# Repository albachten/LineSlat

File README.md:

# LineSlat - Daisy-chained fireworks controllers for line effects

This is an ARM Cortex M0 board with:
* SAMD21 cpu
* USB for programming & serial debug
* Cortex Debug connector for bootloader install & hw debug
* 8 Pairs of PyroClips (8 cues per station)
* 2 RJ45 connectors for daisy-chaining (power & serial comm)
* 915MHz Hope RFM95 Lora module (only populated in the master station)
* Powered by 18V external LiPo battery pack (master station only, slave stations are powered by the master station)
* OLED display

Note: this board can also be used as an 8 cue standalone fireworks controller.

[Schematic pdf](v2.0/LineSlat.pdf)

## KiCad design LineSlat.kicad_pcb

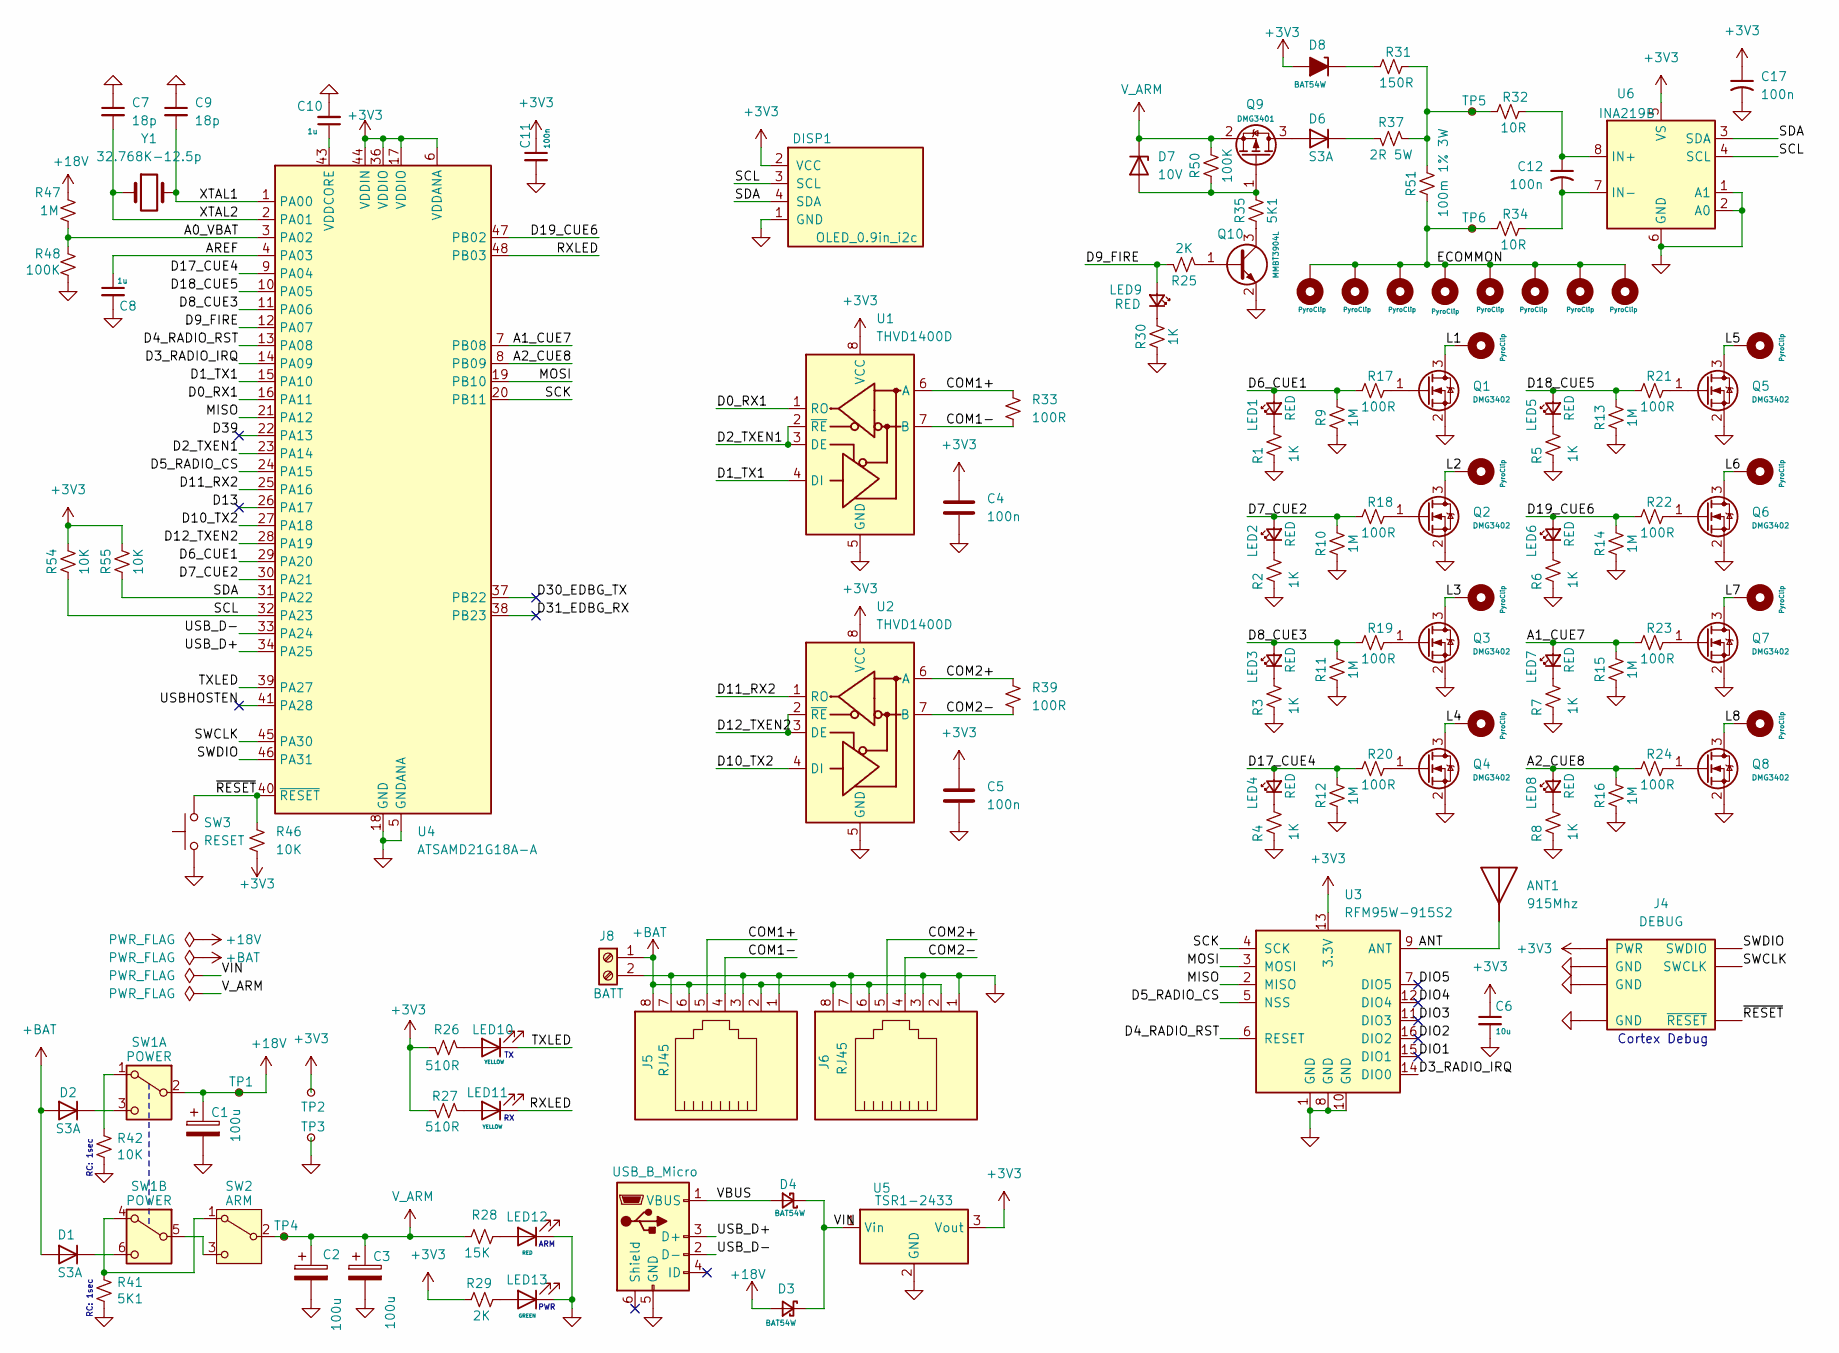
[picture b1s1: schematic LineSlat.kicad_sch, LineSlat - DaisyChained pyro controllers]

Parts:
ANT1: 915Mhz; Antenna915MHzSimpleCoil; Manufacturer_Part_Number 4269; Mouser Part Number 485-4269
C1, C2, C3: 100u; CP_Radial_D6.3mm_P2.50mm; Mouser_Part_Number 710-860010573007
C4, C5, C11, C12, C17: 100n; C_0603_1608Metric
C6: 10u; C_0603_1608Metric
C7, C9: 18p; C_0603_1608Metric
C8, C10: 1u; C_0603_1608Metric
CLIP1, CLIP2, CLIP3, CLIP4, CLIP5, CLIP6, CLIP7, CLIP8: PyroClip; PyroClipBlack; Mouser_Part_Number N/A
CLIP9, CLIP10, CLIP11, CLIP12, CLIP13, CLIP14, CLIP15, CLIP16: PyroClip; PyroClipRed; Mouser_Part_Number N/A
D1, D2, D6: S3A; D_SMC; Mouser_Part_Number 512-S3A
D3, D4, D8: BAT54W; D_SOD-123; Mouser_Part_Number 78-BAT54W-HG3-18
D7: 10V; SOT-23; Mouser_Part_Number 863-BZX84C10LT1G
DISP1: OLED_0.9in_i2c; OLED_0.9in_i2c_weewooday; Mouser_Part_Number N/A
J4: DEBUG; CortexDebugSMD; Mouser_Part_Number 640-BD12510A305580LB
J5, J6: RJ45; RJ45_SS-700810-NF; Mouser_Part_Number 530-SS-700810-NF
J7: USB_B_Micro; USB_Micro-B_Amphenol_10118194_Horizontal; Mouser_Part_Number 649-10118194-0011LF
J8: BATT; TerminalBlock_1x02_P5.08mm; Mouser_Part_Number 649-VI02215200J0G
LED1, LED2, LED3, LED4, LED5, LED6, LED7, LED8, LED9, LED12: RED; LED_0805_2012Metric; Mouser_Part_Number 710-150080RS75000
LED10, LED11: YELLOW; LED_0805_2012Metric; Mouser_Part_Number 710-150080YS75000
LED13: GREEN; LED_0805_2012Metric; Mouser_Part_Number 710-150080RS75000
Q1, Q2, Q3, Q4, Q5, Q6, Q7, Q8: DMG3402; SOT-23; Mouser_Part_Number 621-DMG3402L-7
Q9: DMG3401; SC-59; Mouser_Part_Number 621-DMP3099L-13
Q10: MMBT3904L; SOT-23; Mouser_Part_Number 771-MMBT3904VL
R1, R2, R3, R4, R5, R6, R7, R8, R30: 1K; R_0603_1608Metric
R9, R10, R11, R12, R13, R14, R15, R16, R47: 1M; R_0603_1608Metric
R17, R18, R19, R20, R21, R22, R23, R24, R33, R39: 100R; R_0603_1608Metric
R25, R29: 2K; R_0603_1608Metric
R26, R27: 510R; R_0603_1608Metric
R28: 15K; R_0603_1608Metric
R31: 150R; R_0603_1608Metric
R32, R34: 10R; R_0603_1608Metric
R35, R41: 5K1; R_0603_1608Metric
R37: 2R 5W; R_Axial_Power_L25.0mm_W6.4mm_P27.94mm; Mouser_Part_Number 588-TUW5J2R0E
R42, R46, R54, R55: 10K; R_0603_1608Metric
R48, R50: 100K; R_0603_1608Metric
R51: 100m 1% 3W; R_2512_6332Metric
SW1: POWER; DPDT-SW-T2-4E-B-A2-MA2; Mouser_Part_Number 737-SWT24EBA2MA2
SW2: ARM; SPDT-SW-T2-2E-A-A2-M1; Mouser_Part_Number 737-SW-T2-2E-A-A2-M1
SW3: RESET; TL3305B_SPST_PushButton; Mouser_Part_Number 652-CR0805JW-104ELF
TP1, TP2, TP3, TP4, TP5, TP6: RCTCTE; Mouser_Part_Number 660-RCTCTE
U1, U2: THVD1400D; SOIC-8_3.9x4.9mm_P1.27mm; Mouser_Part_Number 595-THVD1400DR
U3: RFM95W-915S2; RFM95CW; Mouser_Part_Number 223-RFM95W-915S2
U4: ATSAMD21G18A-A; TQFP-48_7x7mm_P0.5mm; Mouser_Part_Number 556-ATSAMD21G18A-MU
U5: TSR1-2433; Converter_DCDC_TRACO_TSR-1_THT; Mouser_Part_Number 495-TSR-1-2433
U6: INA219B; SOIC-8_3.9x4.9mm_P1.27mm; Mouser_Part_Number 595-INA219BIDR
Y1: 32.768K-12.5p; Crystal_SMD_G8-2Pin_3.2x1.5mm; Mouser_Part_Number 520-327-12.5-34B

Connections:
+3V3: C4.1, C5.1, C6.1, C11.1, C17.1, D8.2 (A), DISP1.2 (VCC), J4.1 (PWR), R26.1, R27.1, R29.1, R46.2, R54.2, R55.2, TP2.1, U1.8 (VCC), U2.8 (VCC), U3.13 (3.3V), U4.6 (VDDANA), U4.17 (VDDIO), U4.36 (VDDIO), U4.44 (VDDIN), U5.3 (Vout), U6.5 (VS)
+18V: C1.1, D3.2 (A), R47.1, SW1.2 (B), TP1.1
+BAT: D1.2 (A), D2.2 (A), J5.2, J5.6, J5.8, J6.2, J6.6, J6.8, J8.1
/A0_VBAT: R47.2, R48.1, U4.3 (PA02)
/A1_CUE7: LED7.2 (A), R15.2, R23.1, U4.7 (PB08)
/A2_CUE8: LED8.2 (A), R16.2, R24.1, U4.8 (PB09)
/ANT: ANT1.1 (A), U3.9 (ANT)
/AREF: C8.1, U4.4 (PA03)
/COM1+: J5.5, R33.1, U1.6 (A)
/COM1-: J5.4, R33.2, U1.7 (B)
/COM2+: J6.5, R39.1, U2.6 (A)
/COM2-: J6.4, R39.2, U2.7 (B)
/D0_RX1: U1.1 (RO), U4.16 (PA11)
/D1_TX1: U1.4 (DI), U4.15 (PA10)
/D2_TXEN1: U1.2 (~RE), U1.3 (DE), U4.23 (PA14)
/D3_RADIO_IRQ: U3.14 (DIO0), U4.14 (PA09)
/D4_RADIO_RST: U3.6 (RESET), U4.13 (PA08)
/D5_RADIO_CS: U3.5 (NSS), U4.24 (PA15)
/D6_CUE1: LED1.2 (A), R9.2, R17.1, U4.29 (PA20)
/D7_CUE2: LED2.2 (A), R10.2, R18.1, U4.30 (PA21)
/D8_CUE3: LED3.2 (A), R11.2, R19.1, U4.11 (PA06)
/D9_FIRE: LED9.2 (A), R25.1, U4.12 (PA07)
/D10_TX2: U2.4 (DI), U4.27 (PA18)
/D11_RX2: U2.1 (RO), U4.25 (PA16)
/D12_TXEN2: U2.2 (~RE), U2.3 (DE), U4.28 (PA19)
/D13: U4.26 (PA17)
/D17_CUE4: LED4.2 (A), R12.2, R20.1, U4.9 (PA04)
/D18_CUE5: LED5.2 (A), R13.2, R21.1, U4.10 (PA05)
/D19_CUE6: LED6.2 (A), R14.2, R22.1, U4.47 (PB02)
/D30_EDBG_TX: U4.37 (PB22)
/D31_EDBG_RX: U4.38 (PB23)
/D39: U4.22 (PA13)
/DIO1: U3.15 (DIO1)
/DIO2: U3.16 (DIO2)
/DIO3: U3.11 (DIO3)
/DIO4: U3.12 (DIO4)
/DIO5: U3.7 (DIO5)
/ECOMMON: CLIP9.1, CLIP10.1, CLIP11.1, CLIP12.1, CLIP13.1, CLIP14.1, CLIP15.1, CLIP16.1, R34.1, R51.1, TP6.1
/L1: CLIP1.1, Q1.3 (D)
/L2: CLIP2.1, Q2.3 (D)
/L3: CLIP3.1, Q3.3 (D)
/L4: CLIP4.1, Q4.3 (D)
/L5: CLIP5.1, Q5.3 (D)
/L6: CLIP6.1, Q6.3 (D)
/L7: CLIP7.1, Q7.3 (D)
/L8: CLIP8.1, Q8.3 (D)
/MISO: U3.2 (MISO), U4.21 (PA12)
/MOSI: U3.3 (MOSI), U4.19 (PB10)
/RXLED: LED11.1 (K), U4.48 (PB03)
/SCK: U3.4 (SCK), U4.20 (PB11)
/SCL: DISP1.3 (SCL), R54.1, U4.32 (PA23), U6.4 (SCL)
/SDA: DISP1.4 (SDA), R55.1, U4.31 (PA22), U6.3 (SDA)
/SWCLK: J4.4 (SWCLK), U4.45 (PA30)
/SWDIO: J4.2 (SWDIO), U4.46 (PA31)
/TXLED: LED10.1 (K), U4.39 (PA27)
/USBHOSTEN: U4.41 (PA28)
/USB_D+: J7.3 (D+), U4.34 (PA25)
/USB_D-: J7.2 (D-), U4.33 (PA24)
/VBUS: D4.2 (A), J7.1 (VBUS)
/VIN: D3.1 (K), D4.1 (K), U5.1 (Vin)
/XTAL1: C9.2, U4.1 (PA00), Y1.2
/XTAL2: C7.2, U4.2 (PA01), Y1.1
/~RESET: J4.10 (~RESET), R46.1, SW3.2, U4.40 (~RESET)
GND: C1.2, C2.2, C3.2, C4.2, C5.2, C6.2, C7.1, C8.2, C9.1, C10.2, C11.2, C17.2, DISP1.1 (GND), J4.3 (GND), J4.5 (GND), J4.9 (GND), J5.1, J5.3, J5.7, J6.1, J6.3, J6.7, J7.5 (GND), J8.2, LED12.1 (K), LED13.1 (K), Q1.2 (S), Q2.2 (S), Q3.2 (S), Q4.2 (S), Q5.2 (S), Q6.2 (S), Q7.2 (S), Q8.2 (S), Q10.2 (E), R1.1, R2.1, R3.1, R4.1, R5.1, R6.1, R7.1, R8.1, R9.1, R10.1, R11.1, R12.1, R13.1, R14.1, R15.1, R16.1, R30.1, R41.1, R42.1, R48.2, SW3.1, TP3.1, U1.5 (GND), U2.5 (GND), U3.1 (GND), U3.8 (GND), U3.10 (GND), U4.5 (GNDANA), U4.18 (GND), U4.35 (GND), U4.42 (GND), U5.2 (GND), U6.1 (A1), U6.2 (A0), U6.6 (GND)
unnamed: D1.1 (K), SW1.6 (C)
unnamed: D2.1 (K), SW1.3 (C)
unnamed: D6.2 (A), Q9.3 (D)
unnamed: D6.1 (K), R37.2
unnamed: D7.1 (A), Q9.1 (G), R35.2, R50.1
unnamed: D8.1 (K), R31.1
unnamed: LED1.1 (K), R1.2
unnamed: LED2.1 (K), R2.2
unnamed: LED3.1 (K), R3.2
unnamed: LED4.1 (K), R4.2
unnamed: LED5.1 (K), R5.2
unnamed: LED6.1 (K), R6.2
unnamed: LED7.1 (K), R7.2
unnamed: LED8.1 (K), R8.2
unnamed: LED9.1 (K), R30.2
unnamed: LED10.2 (A), R26.2
unnamed: LED11.2 (A), R27.2
unnamed: LED12.2 (A), R28.2
unnamed: LED13.2 (A), R29.2
unnamed: Q1.1 (G), R17.2
unnamed: Q2.1 (G), R18.2
unnamed: Q3.1 (G), R19.2
unnamed: Q4.1 (G), R20.2
unnamed: Q5.1 (G), R21.2
unnamed: Q6.1 (G), R22.2
unnamed: Q7.1 (G), R23.2
unnamed: Q8.1 (G), R24.2
unnamed: Q10.1 (B), R25.2
unnamed: Q10.3 (C), R35.1
unnamed: R31.2, R32.1, R37.1, R51.2, TP5.1
unnamed: R42.2, SW1.1 (A)
unnamed: R41.2, SW1.4 (A), SW2.1 (A)
unnamed: SW1.5 (B), SW2.3 (C)
unnamed: C10.1, U4.43 (VDDCORE)
unnamed: C12.1, R32.2, U6.8 (IN+)
unnamed: C12.2, R34.2, U6.7 (IN-)
V_ARM: C2.1, C3.1, D7.3 (K), Q9.2 (S), R28.1, R50.2, SW2.2 (B), TP4.1

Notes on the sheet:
PWR
RC: 1sec
ARM
Cortex Debug

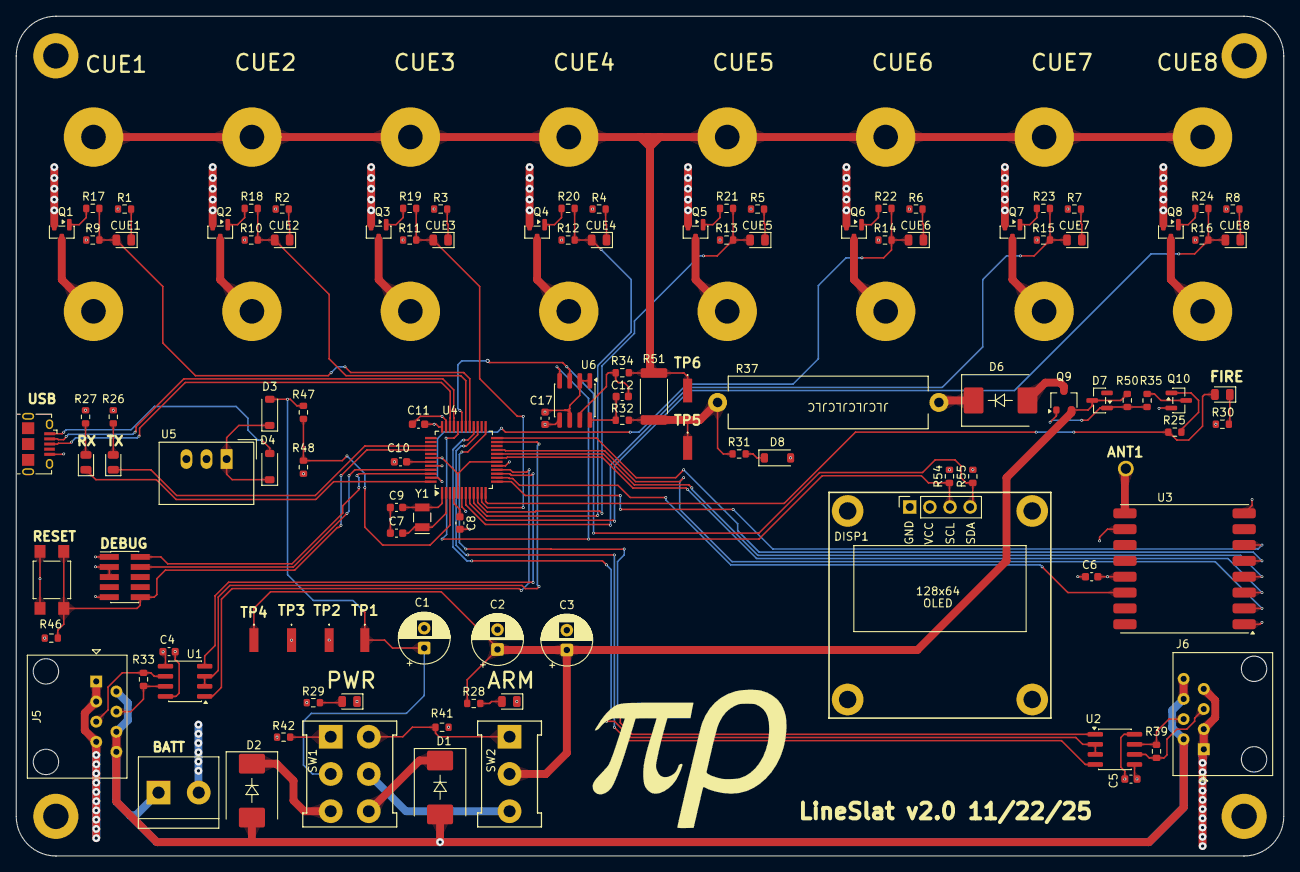
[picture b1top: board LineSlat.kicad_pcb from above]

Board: 4 copper layers, 160.0 x 106.0 mm, 134 parts (1 on the bottom side), 91 nets.

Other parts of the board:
H1, H2, H3, H4: MountingHole_3.2mm_M3_ISO7380_Pad
LOGO1, LOGO2: LOGO; pirho

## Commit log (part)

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2024-12-12 v1.0
2024-12-13 Change diodes and regulator
    Changed regulator from TSR-1-2433E to TSR-1-2433
    This changes Vin minimum from 6V to 4.76V
    Changed schottky diodes to BAT54W.
    This fixes 2 issues:
    - reverse voltage 20V -> 30V (not enough margin for ~20V LiPo)
    - forward voltage drop 600mV -> 250mV (5V-600mV is below Vin min of 3.3V regulator)
2025-11-30 v2.0
    * new continuity test using INA219
    * 8 cues instead of 6
    * Lots of minor changes
